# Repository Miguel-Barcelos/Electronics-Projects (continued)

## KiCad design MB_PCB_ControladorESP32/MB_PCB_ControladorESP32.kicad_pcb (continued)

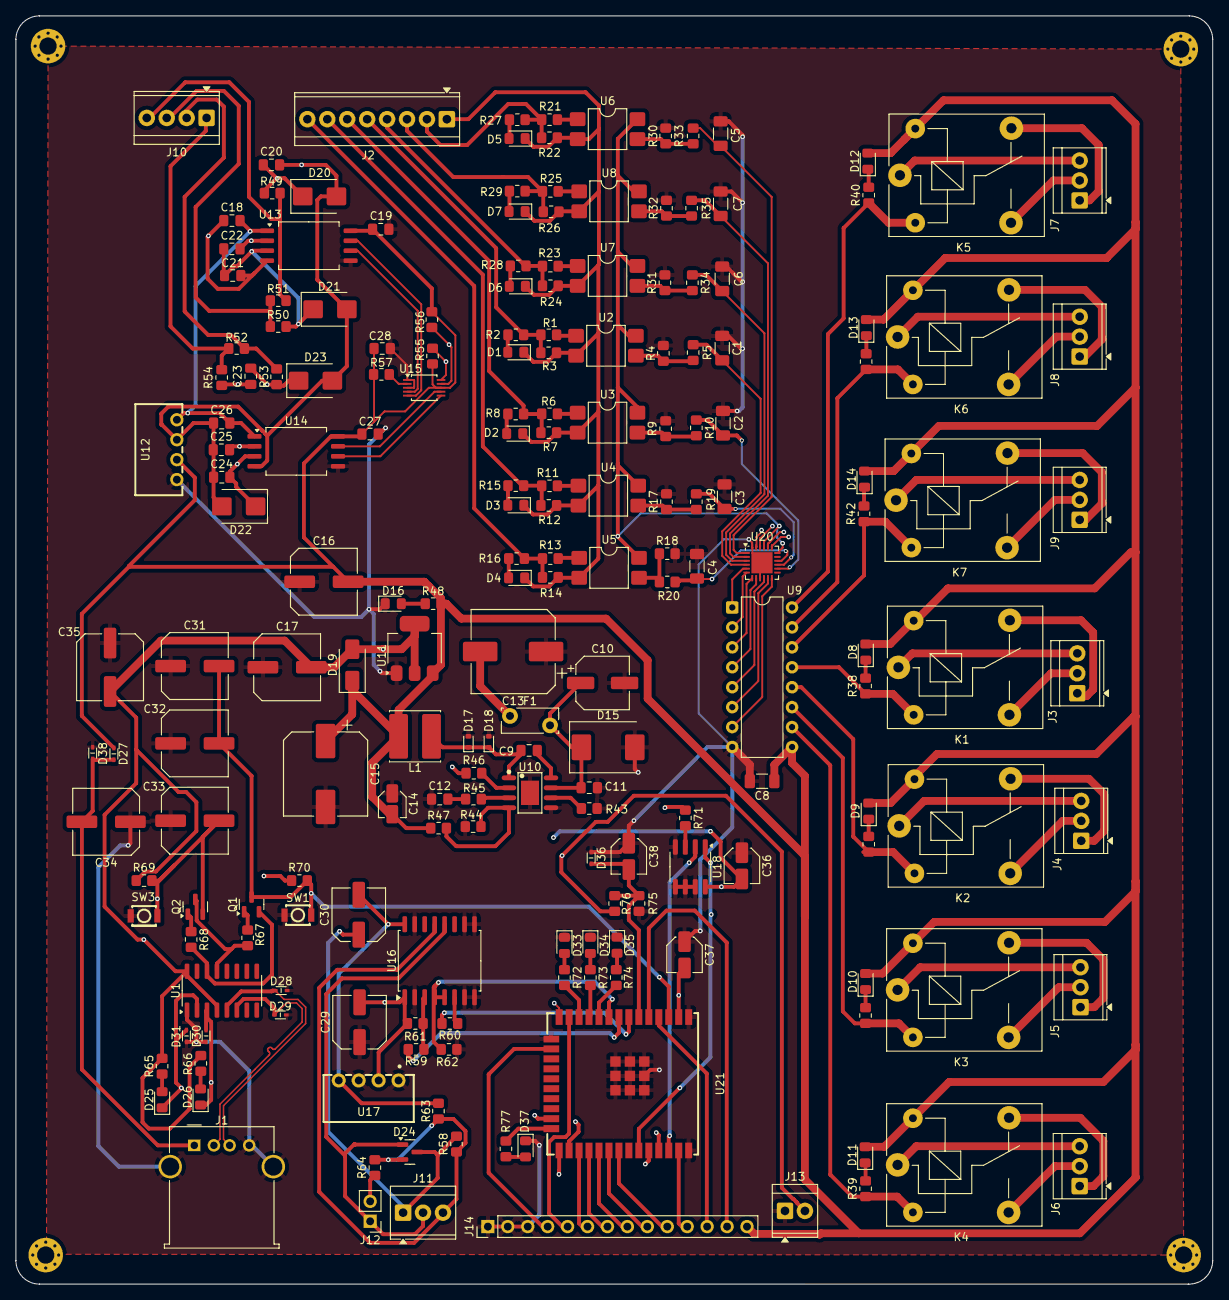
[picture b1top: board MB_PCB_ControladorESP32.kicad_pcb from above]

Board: 4 copper layers, 152.5 x 161.6 mm, 199 parts (0 on the bottom side), 154 nets.

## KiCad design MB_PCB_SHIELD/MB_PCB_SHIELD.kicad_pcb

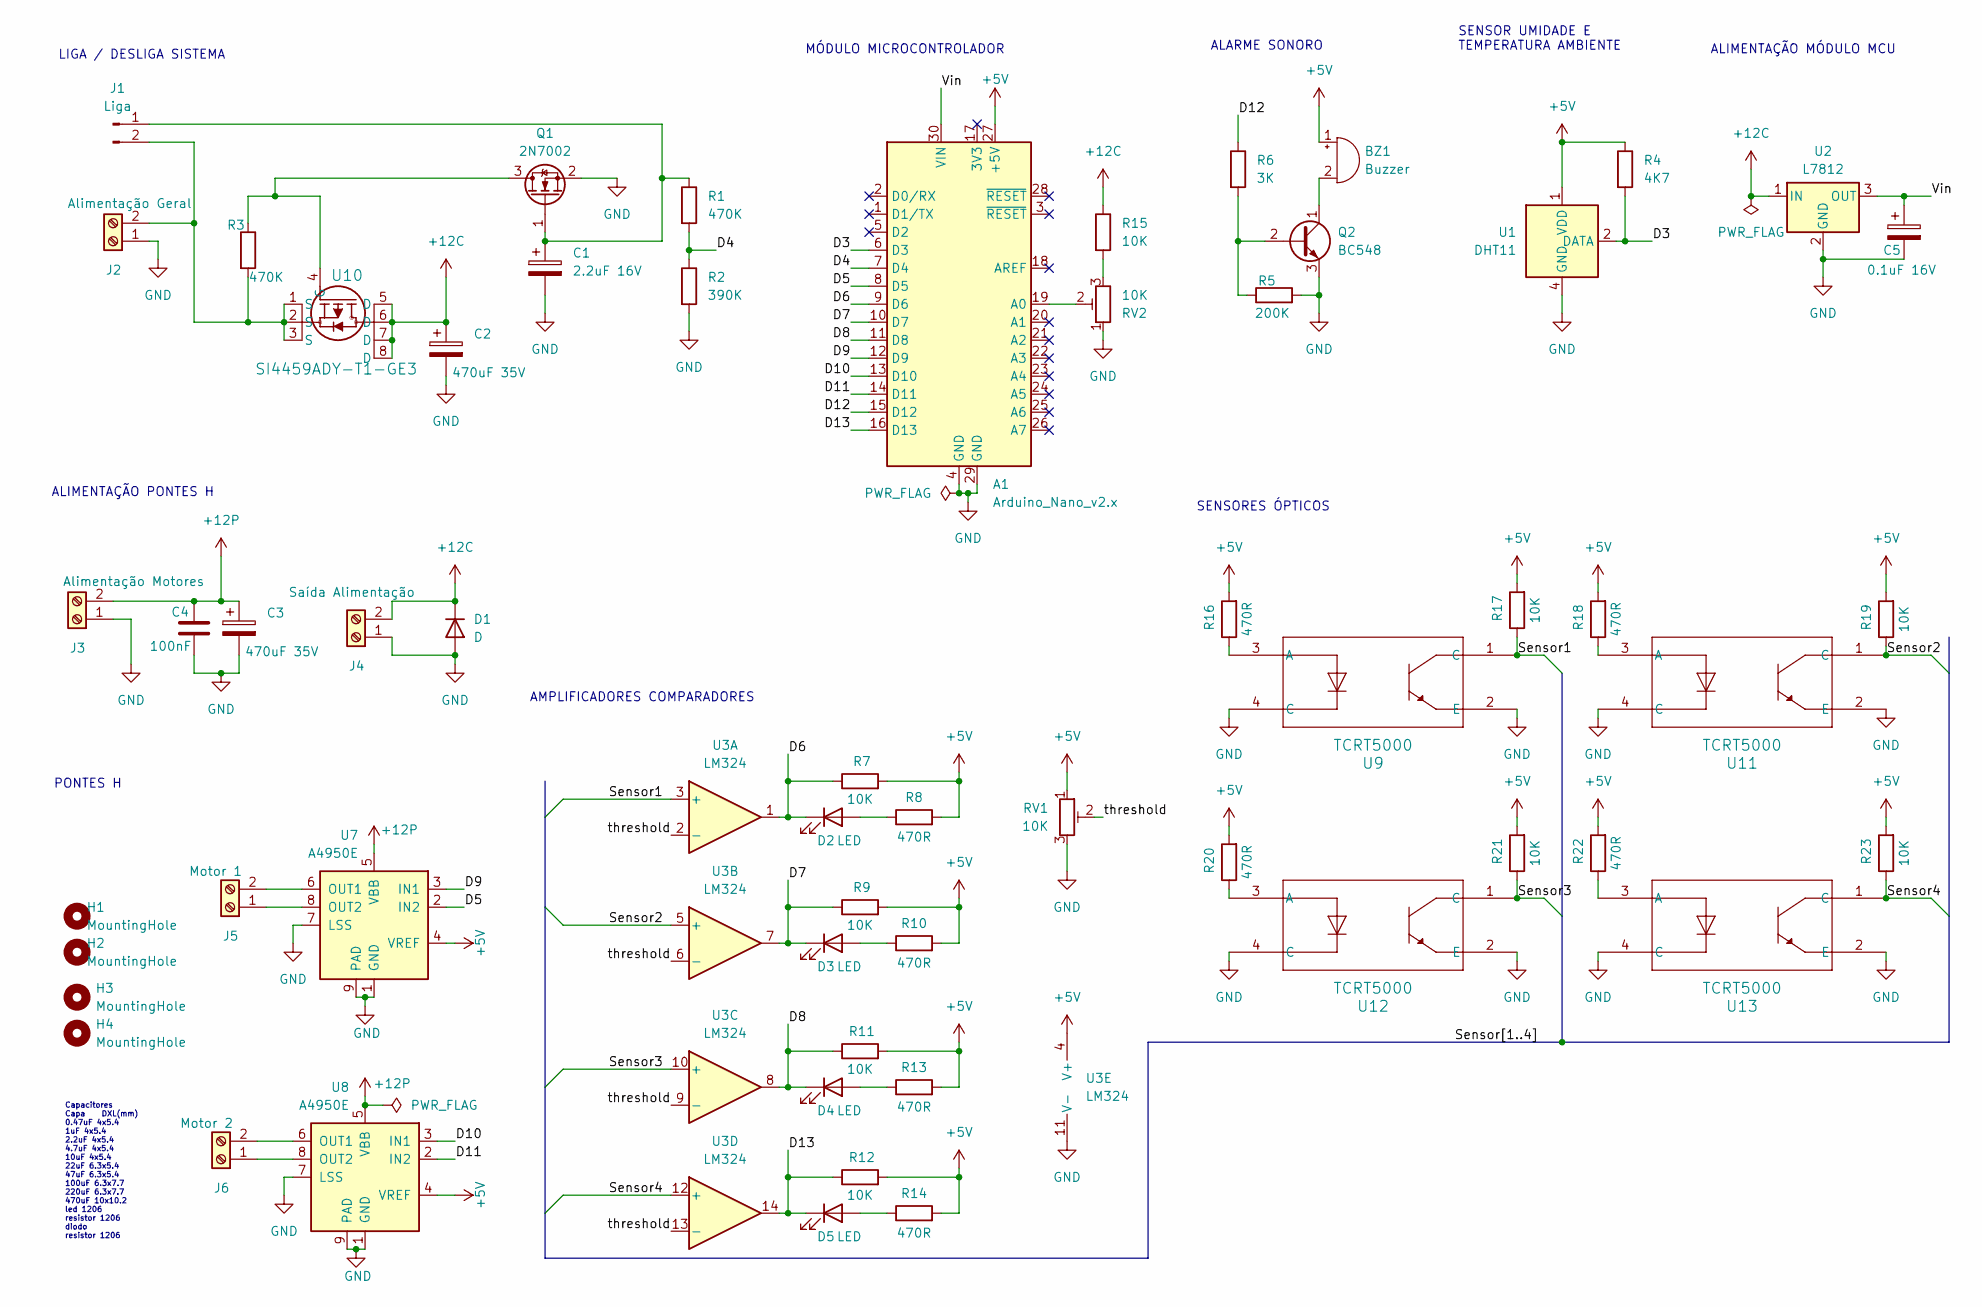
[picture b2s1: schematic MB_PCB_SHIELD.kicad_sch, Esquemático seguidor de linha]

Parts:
A1: Arduino_Nano_v2.x; Arduino_Nano
BZ1: Buzzer; Buzzer_12x9.5RM7.6
C1: 2.2uF 16V; CP_Elec_4x5.3
C2, C3: 470uF 35V; CP_Elec_4x5.3
C4: 100nF; CP_Radial_D10.0mm_P5.00mm
C5: 0.1uF 16V; CP_Elec_4x5.3
D1: D; D_SMA_Handsoldering
D2, D3, D4, D5: LED; LED_1206_3216Metric_Pad1.42x1.75mm_HandSolder
H1, H2, H3, H4: MountingHole; MountingHole_3.2mm_M3_DIN965_Pad
J1: Liga; PinSocket_1x02_P2.54mm_Vertical
J2: Alimentação Geral; TerminalBlock_Phoenix_MKDS-1,5-2-5.08_1x02_P5.08mm_Horizont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
J3: Alimentação Motores; TerminalBlock_Phoenix_MKDS-1,5-2-5.08_1x02_P5.08mm_Horizont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
J4: Saída Alimentação; TerminalBlock_Phoenix_MKDS-1,5-2-5.08_1x02_P5.08mm_Horizont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
J5: Motor 1; TerminalBlock_Phoenix_MKDS-1,5-2-5.08_1x02_P5.08mm_Horizont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
J6: Motor 2; TerminalBlock_Phoenix_MKDS-1,5-2-5.08_1x02_P5.08mm_Horizont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
Q1: 2N7002; SOT-23_Handsoldering
Q2: BC548; TO-92_Inline
R1, R3: 470K; R_1206_3216Metric_Pad1.30x1.75mm_HandSolder
R2: 390K; R_1206_3216Metric_Pad1.30x1.75mm_HandSolder
R4: 4K7; R_1206_3216Metric_Pad1.30x1.75mm_HandSolder
R5: 200K; R_1206_3216Metric_Pad1.30x1.75mm_HandSolder
R6: 3K; R_1206_3216Metric_Pad1.30x1.75mm_HandSolder
R7, R9, R11, R12, R15, R17, R19, R21, R23: 10K; R_1206_3216Metric_Pad1.30x1.75mm_HandSolder
R8, R10, R13, R14, R16, R18, R20, R22: 470R; R_1206_3216Metric_Pad1.30x1.75mm_HandSolder
RV1, RV2: 10K; Potentiometer_ACP_CA9-H2,5_Horizontal
U1: DHT11; Aosong_DHT11_5.5x12.0_P2.54mm
U2: L7812; TO-220-3_Vertical
U3: LM324; SOIC-14_3.9x8.7mm_P1.27mm
U7, U8: A4950E; SOIC-8-1EP_3.9x4.9mm_P1.27mm_EP2.41x3.3mm
U9, U11, U12, U13: TCRT5000; TCRT5000_VIS
U10: SI4459ADY-T1-GE3; SO_ADY-T1-GE3_VIS

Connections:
+5V: A1.27 (+5V), BZ1.1 (+), R4.1, R7.2, R8.2, R9.2, R10.2, R11.2, R12.2, R13.2, R14.2, R16.2, R17.2, R18.2, R19.2, R20.2, R21.2, R22.2, R23.2, RV1.1, U1.1 (VDD), U3.4 (V+), U7.4 (VREF), U8.4 (VREF)
+12C: C2.1, D1.1 (K), J4.2, R15.1, U2.1 (IN), U10.5 (D), U10.6 (D), U10.7 (D), U10.8 (D)
+12P: C3.1, C4.1, J3.2, U7.5 (VBB), U8.5 (VBB)
/D3: A1.6 (D3), R4.2, U1.2 (DATA)
/D4: A1.7 (D4), R1.2, R2.1
/D5: A1.8 (D5), U7.2 (IN2)
/D6: A1.9 (D6), D2.1 (K), R7.1, U3.1
/D7: A1.10 (D7), D3.1 (K), R9.1, U3.7
/D8: A1.11 (D8), D4.1 (K), R11.1, U3.8
/D9: A1.12 (D9), U7.3 (IN1)
/D10: A1.13 (D10), U8.3 (IN1)
/D11: A1.14 (D11), U8.2 (IN2)
/D12: A1.15 (D12), R6.1
/D13: A1.16 (D13), D5.1 (K), R12.1, U3.14
/Sensor1: R17.1, U3.3 (+), U9.1 (C)
/Sensor2: R19.1, U3.5 (+), U11.1 (C)
/Sensor3: R21.1, U3.10 (+), U12.1 (C)
/Sensor4: R23.1, U3.12 (+), U13.1 (C)
/Vin: A1.30 (VIN), C5.1, U2.3 (OUT)
/threshold: RV1.2, U3.2 (-), U3.6 (-), U3.9 (-), U3.13 (-)
GND: A1.4 (GND), A1.29 (GND), C1.2, C2.2, C3.2, C4.2, C5.2, D1.2 (A), J2.1, J3.1, J4.1, Q1.2 (S), Q2.3 (E), R2.2, R5.2, RV1.3, RV2.1, U1.4 (GND), U2.2 (GND), U3.11 (V-), U7.1 (GND), U7.7 (LSS), U7.9 (PAD), U8.1 (GND), U8.7 (LSS), U8.9 (PAD), U9.2 (E), U9.4 (C), U11.2 (E), U11.4 (C), U12.2 (E), U12.4 (C), U13.2 (E), U13.4 (C)
unnamed: A1.19 (A0), RV2.2
unnamed: BZ1.2 (-), Q2.1 (C)
unnamed: D2.2 (A), R8.1
unnamed: D3.2 (A), R10.1
unnamed: D4.2 (A), R13.1
unnamed: D5.2 (A), R14.1
unnamed: C1.1, J1.1, Q1.1 (G), R1.1
unnamed: J1.2, J2.2, R3.2, U10.1 (S), U10.2 (S), U10.3 (S)
unnamed: J5.1, U7.8 (OUT2)
unnamed: J5.2, U7.6 (OUT1)
unnamed: J6.1, U8.8 (OUT2)
unnamed: J6.2, U8.6 (OUT1)
unnamed: Q1.3 (D), R3.1, U10.4 (G)
unnamed: Q2.2 (B), R5.1, R6.2
unnamed: R15.2, RV2.3
unnamed: R16.1, U9.3 (A)
unnamed: R18.1, U11.3 (A)
unnamed: R20.1, U12.3 (A)
unnamed: R22.1, U13.3 (A)

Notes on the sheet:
SENSORES ÓPTICOS
ALIMENTAÇÃO PONTES H
ALIMENTAÇÃO MÓDULO MCU
ALARME SONORO
MÓDULO MICROCONTROLADOR
SENSOR UMIDADE E TEMPERATURA AMBIENTE
AMPLIFICADORES COMPARADORES
PONTES H
Capacitores Capa DXL(mm) 0.47uF 4x5.4 1uF 4x5.4 2.2uF 4x5.4 4.7uF 4x5.4 10uF 4x5.4 22uF 6.3x5.4 47uF 6.3x5.4 100uF 6.3x7.7 220uF 6.3x7.7 470uF 10x10.2 led 1206 resistor 1206 diodo resistor 1206
LIGA / DESLIGA SISTEMA

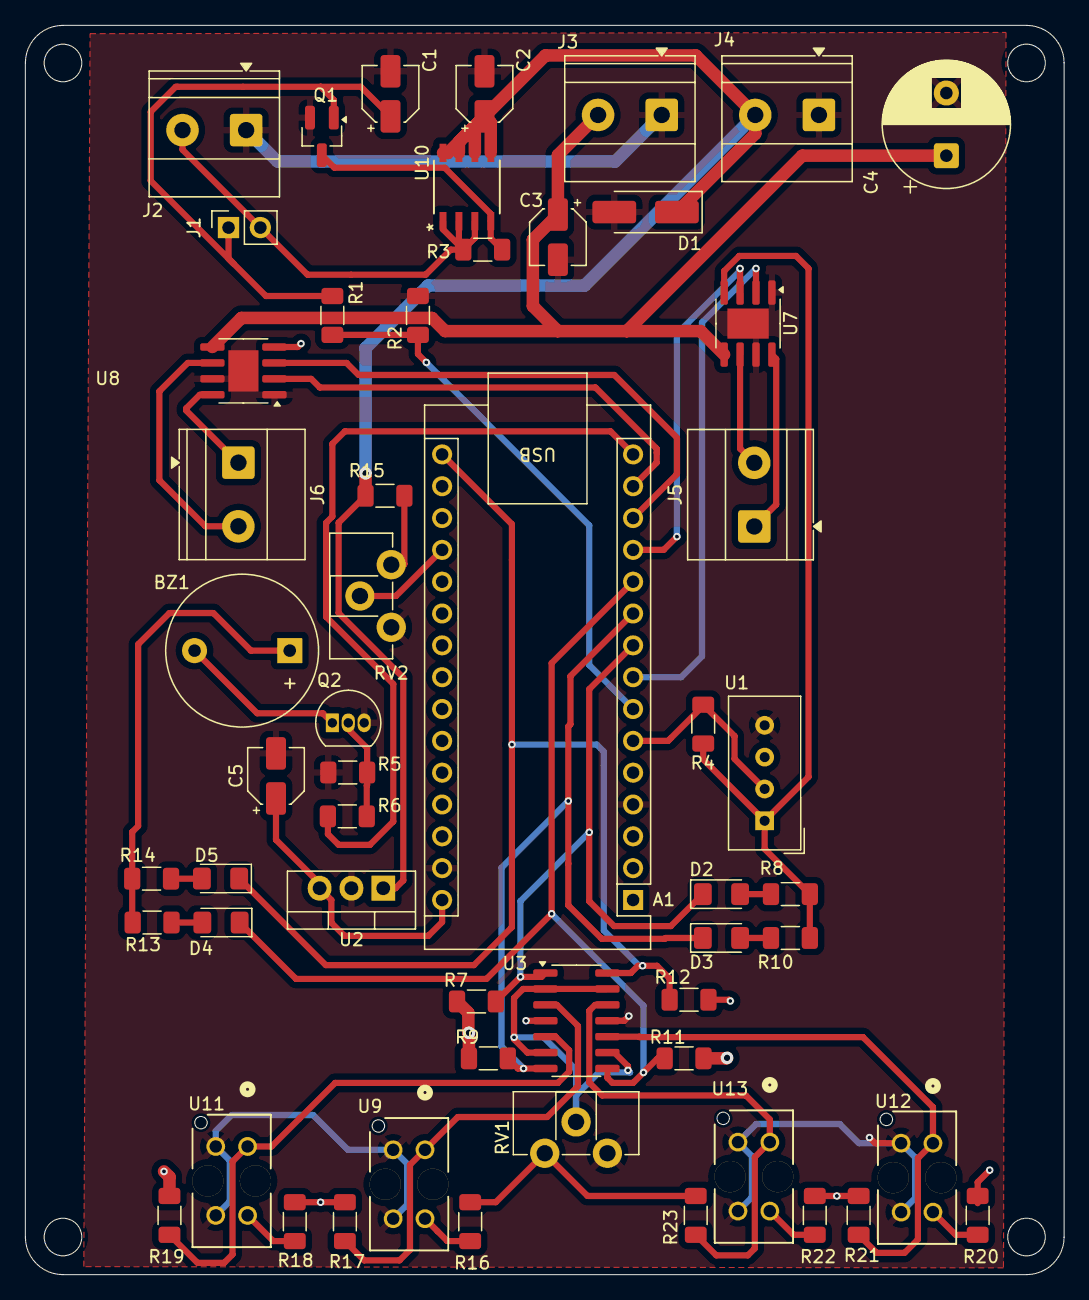
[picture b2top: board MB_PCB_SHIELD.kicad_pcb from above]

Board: 2 copper layers, 82.9 x 99.7 mm, 55 parts (0 on the bottom side), 40 nets.

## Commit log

2026-06-04 Atualização de projeto.
